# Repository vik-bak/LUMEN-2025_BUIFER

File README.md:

# LUMEN-2025_BUIFER
Development of the hardware and software for smart protection helmet used by construction workers. Three PCBs were design in order to expand the functionalities of the regular protection helmet, code-named after their location on the helmet: BackPCB, FrontPCB and SidePCB. Code written in C, built and loaded into the STM32L476 and ESP Wrover microcontrollers. Implemented local web application developed in React to visualize data from sensors and to notify user about important informations on the construction site. The whole system was tested and proved functional and efficient.

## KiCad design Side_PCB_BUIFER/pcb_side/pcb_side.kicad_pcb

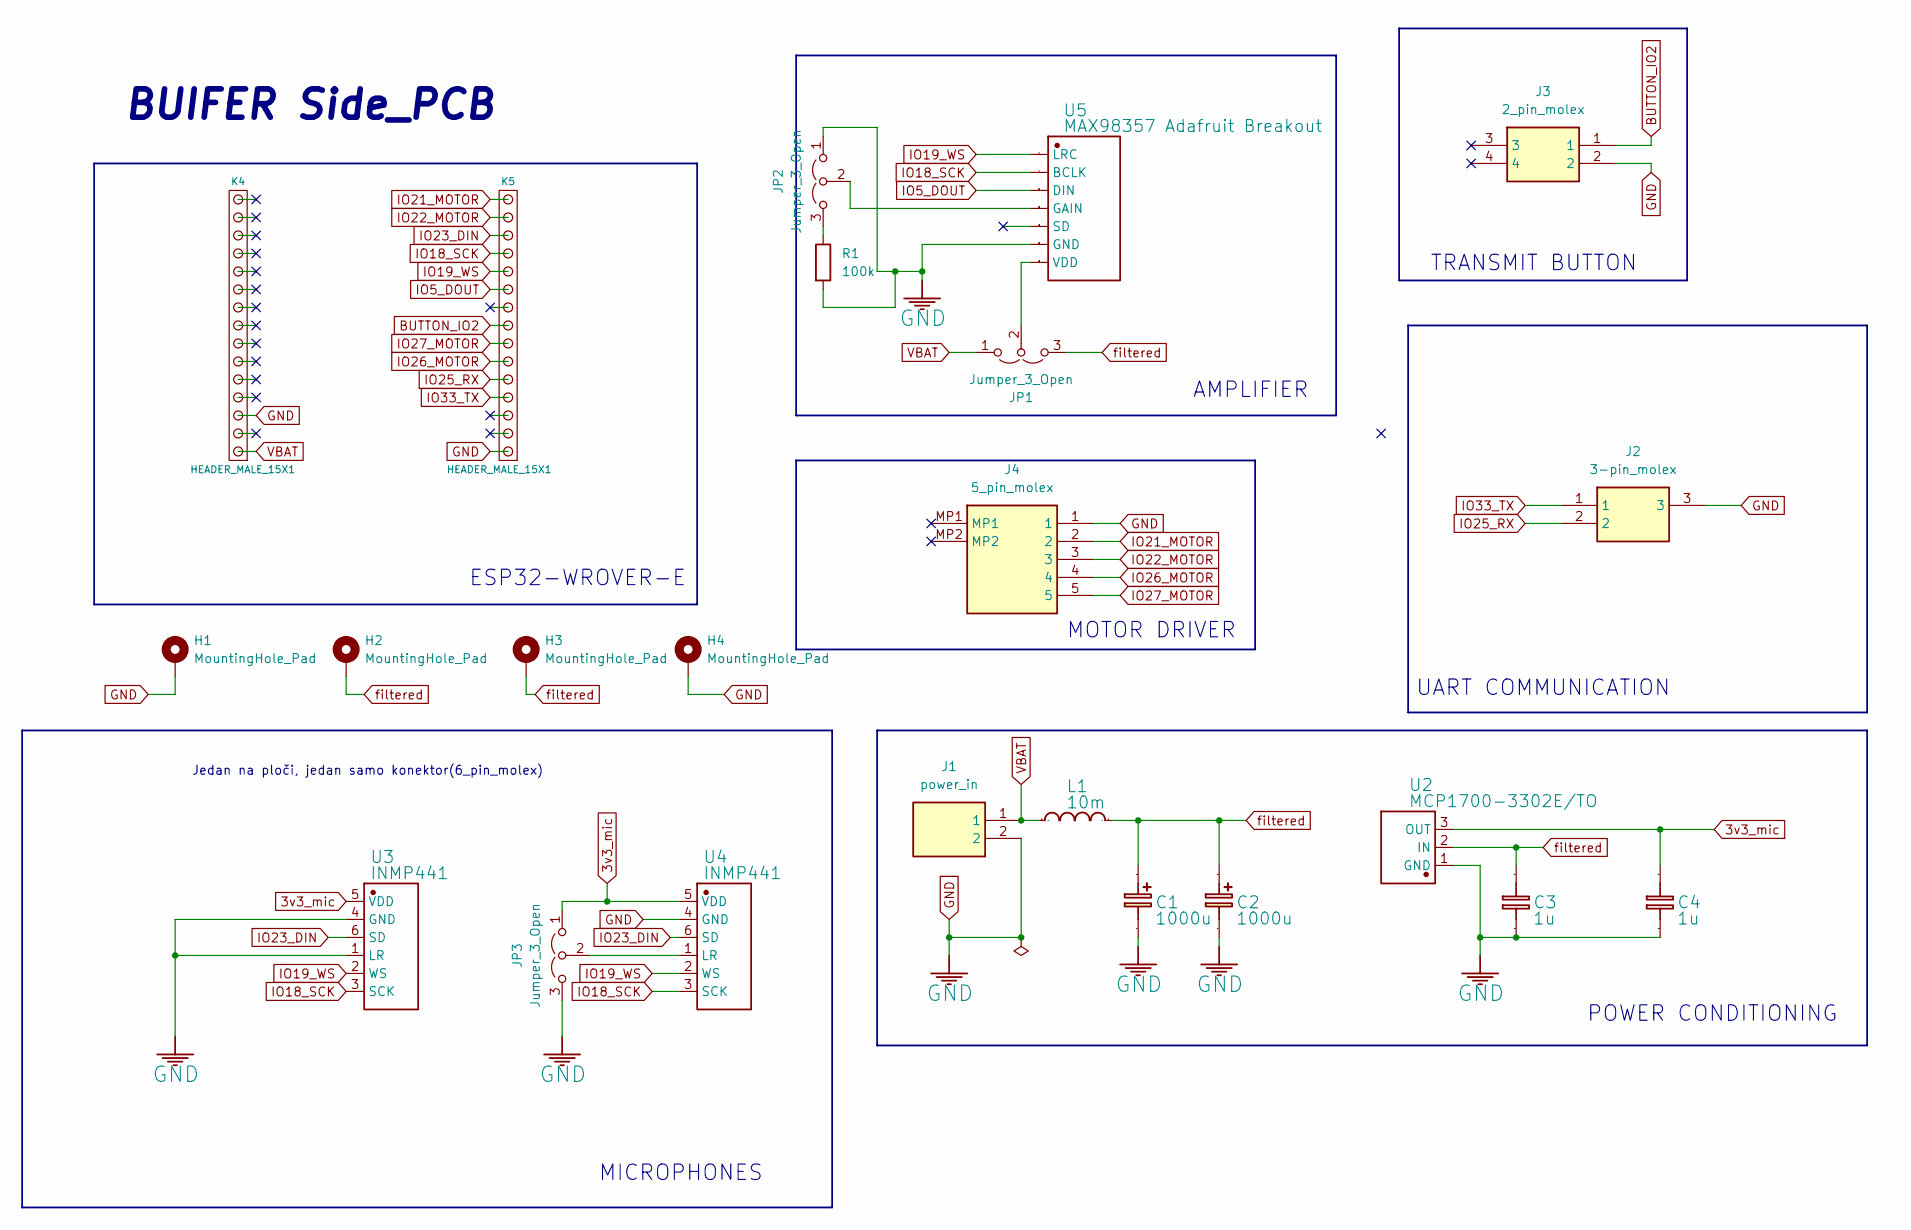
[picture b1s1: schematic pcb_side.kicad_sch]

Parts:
C1, C2: 1000u; CP_Elec_10x12.5
C3, C4: 1u; C_0603_1608Metric_Pad1.08x0.95mm_HandSolder
H1, H2, H3, H4: MountingHole_Pad; MountingHole_2.5mm_Pad_Via
J1: power_in; Mouser Part Number 538-215760-3002
J2: 3-pin_molex; 3_pin_molex; Mouser Part Number 538-53398-0376
J3: 2_pin_molex; Mouser Part Number 538-53398-0276
J4: 5_pin_molex; Mouser Part Number 538-53261-0571
JP1, JP2, JP3: Jumper_3_Open; PinHeader_1x03_P1.27mm_Vertical
K4, K5: HEADER_MALE_15X1; PinSocket_1x15_P2.54mm_Vertical
L1: 10m; L_Radial_D8.7mm_P5.00mm_Fastron_07HCP
R1: 100k; R_0603_1608Metric_Pad0.98x0.95mm_HandSolder
U2: MCP1700-3302E/TO; 3v3_ldo; Manufacturer Part MCP1700-3302E/TO
U3: INMP441; 6_pin_molex
U4: INMP441
U5: MAX98357 Adafruit Breakout; MAX98357A ADAFRUIT

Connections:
3v3_mic: C4.2, JP3.1 (A), U2.3 (OUT), U3.5 (VDD), U4.5 (VDD)
BUTTON_IO2: J3.1, K5.8
GND: C1.2, C2.2, C3.1, C4.1, H1.1, H4.1, J1.2, J2.3, J3.2, J4.1, JP2.1 (A), JP3.3 (B), K4.3, K5.1, R1.2, U2.1 (GND), U3.1 (LR), U3.4 (GND), U4.4 (GND), U5.13 (GND)
IO5_DOUT: K5.10, U5.10 (DIN)
IO18_SCK: K5.12, U3.3 (SCK), U4.3 (SCK), U5.9 (BCLK)
IO19_WS: K5.11, U3.2 (WS), U4.2 (WS), U5.8 (LRC)
IO21_MOTOR: J4.2, K5.15
IO22_MOTOR: J4.3, K5.14
IO23_DIN: K5.13, U3.6 (SD), U4.6 (SD)
IO25_RX: J2.2, K5.5
IO26_MOTOR: J4.4, K5.6
IO27_MOTOR: J4.5, K5.7
IO33_TX: J2.1, K5.4
unnamed: JP1.2 (C), U5.14 (VDD)
unnamed: JP2.3 (B), R1.1
unnamed: JP2.2 (C), U5.11 (GAIN)
unnamed: JP3.2 (C), U4.1 (LR)
VBAT: J1.1, JP1.1 (A), K4.1, L1.1
filtered: C1.1, C2.1, C3.2, H2.1, H3.1, JP1.3 (B), L1.2, U2.2 (IN)

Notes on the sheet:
AMPLIFIER
TRANSMIT BUTTON
Jedan na ploči, jedan samo konektor(6_pin_molex)
ESP32-WROVER-E
BUIFER Side_PCB
MOTOR DRIVER
UART COMMUNICATION
POWER CONDITIONING
MICROPHONES

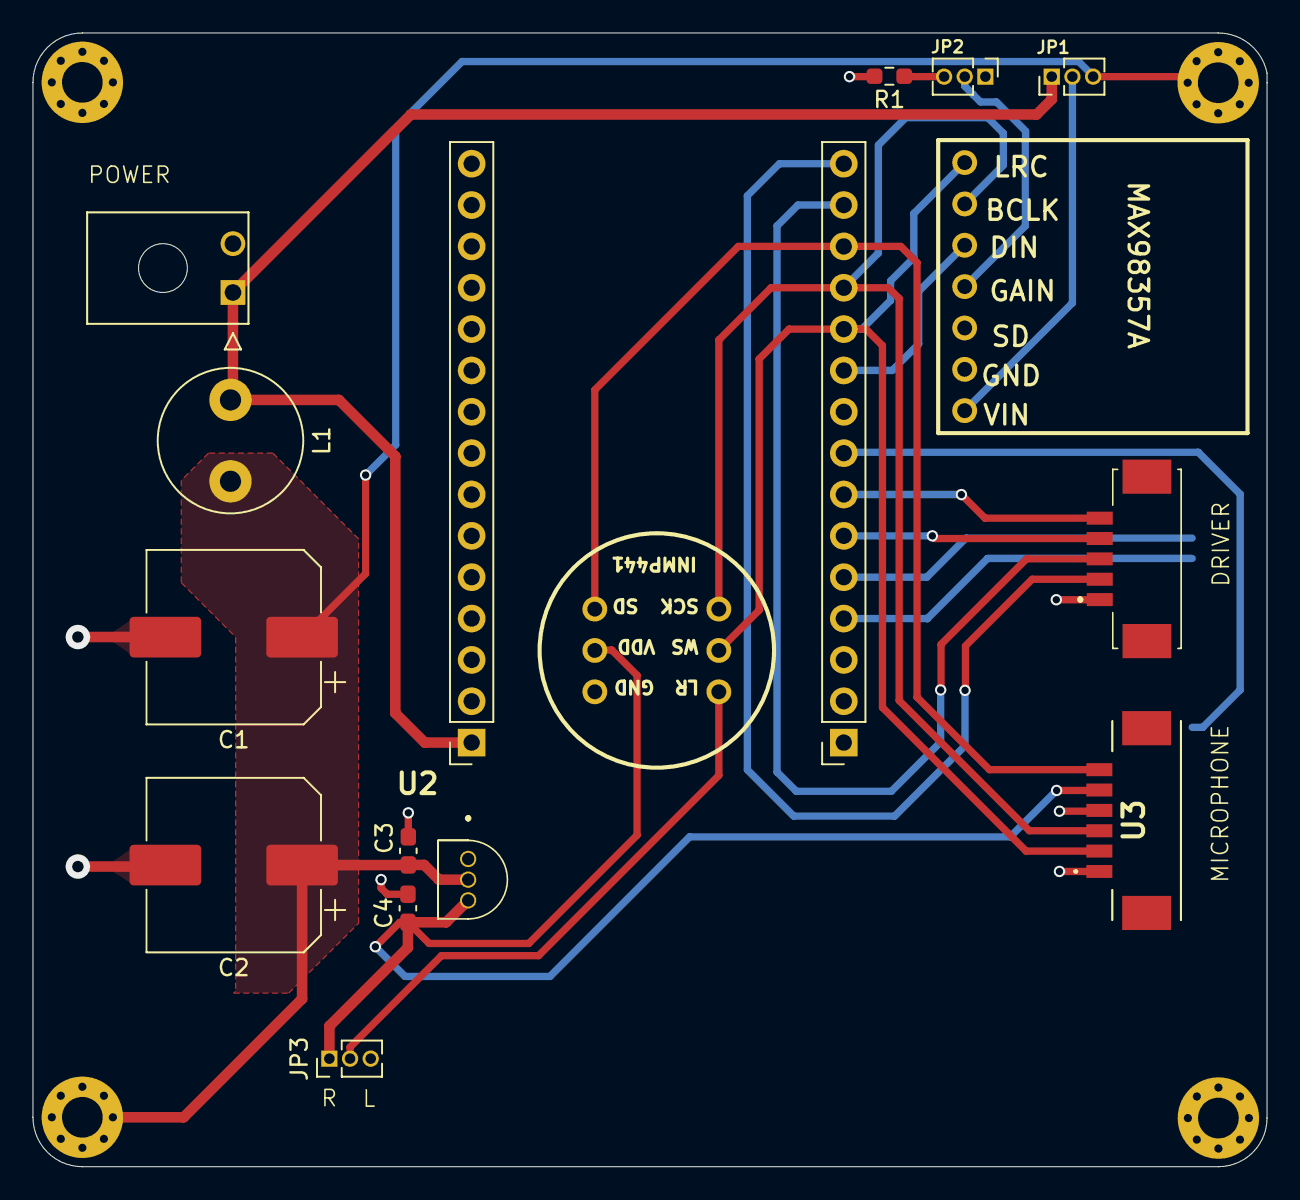
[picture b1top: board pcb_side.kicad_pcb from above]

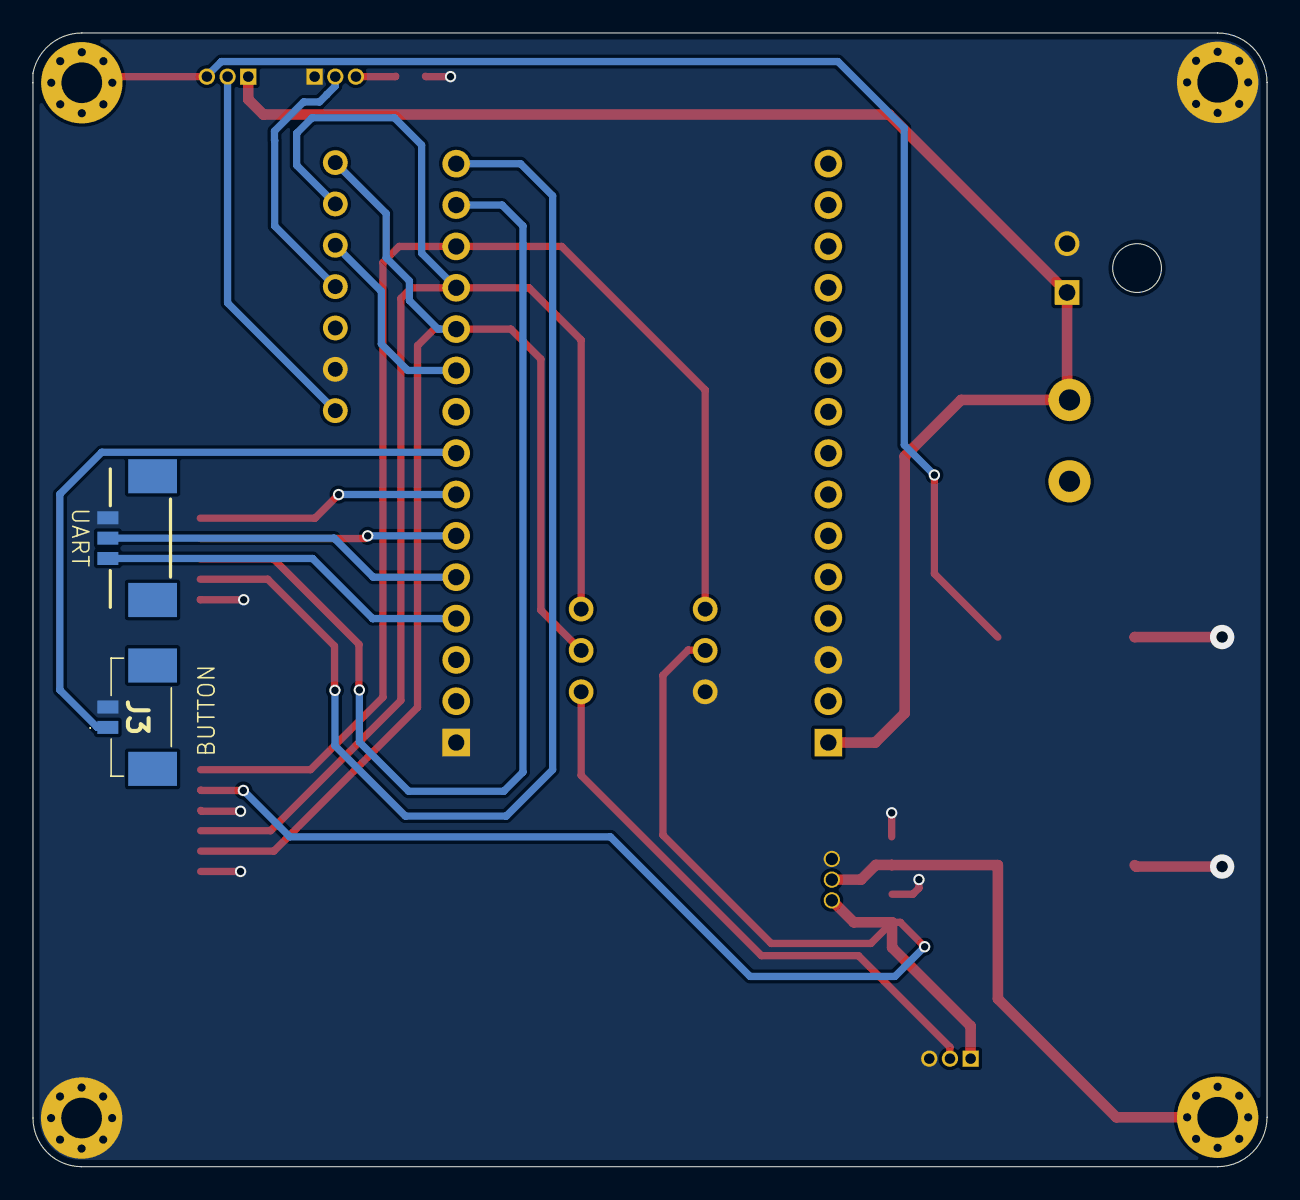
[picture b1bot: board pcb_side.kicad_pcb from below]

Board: 2 copper layers, 75.8 x 69.6 mm, 23 parts (2 on the bottom side), 19 nets.

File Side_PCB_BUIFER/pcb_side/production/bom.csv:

Designator,Footprint,Quantity,Value,LCSC Part #
"C1, C2",CP_Elec_10x12.5,2,1000u,
"C3, C4",0603,2,1u,
"H1, H2, H3, H4",MountingHole_2.5mm_Pad_Via,4,MountingHole_Pad,
J1,power_in,1,power_in,
J2,3_pin_molex,1,3-pin_molex,
J3,2_pin_molex,1,2_pin_molex,
J4,5_pin_molex,1,5_pin_molex,
"JP1, JP2, JP3",PinHeader_1x03_P1.27mm_Vertical,3,Jumper_3_Open,
"K4, K5",PinSocket_1x15_P2.54mm_Vertical,2,HEADER_MALE_15X1,
L1,L_Radial_D8.7mm_P5.00mm_Fastron_07HCP,1,10m,
R1,0603,1,100k,
U2,3v3_ldo,1,MCP1700-3302E/TO,
U3,6_pin_molex,1,INMP441,
U4,INMP441,1,INMP441,
U5,MAX98357A ADAFRUIT,1,MAX98357 Adafruit Breakout,

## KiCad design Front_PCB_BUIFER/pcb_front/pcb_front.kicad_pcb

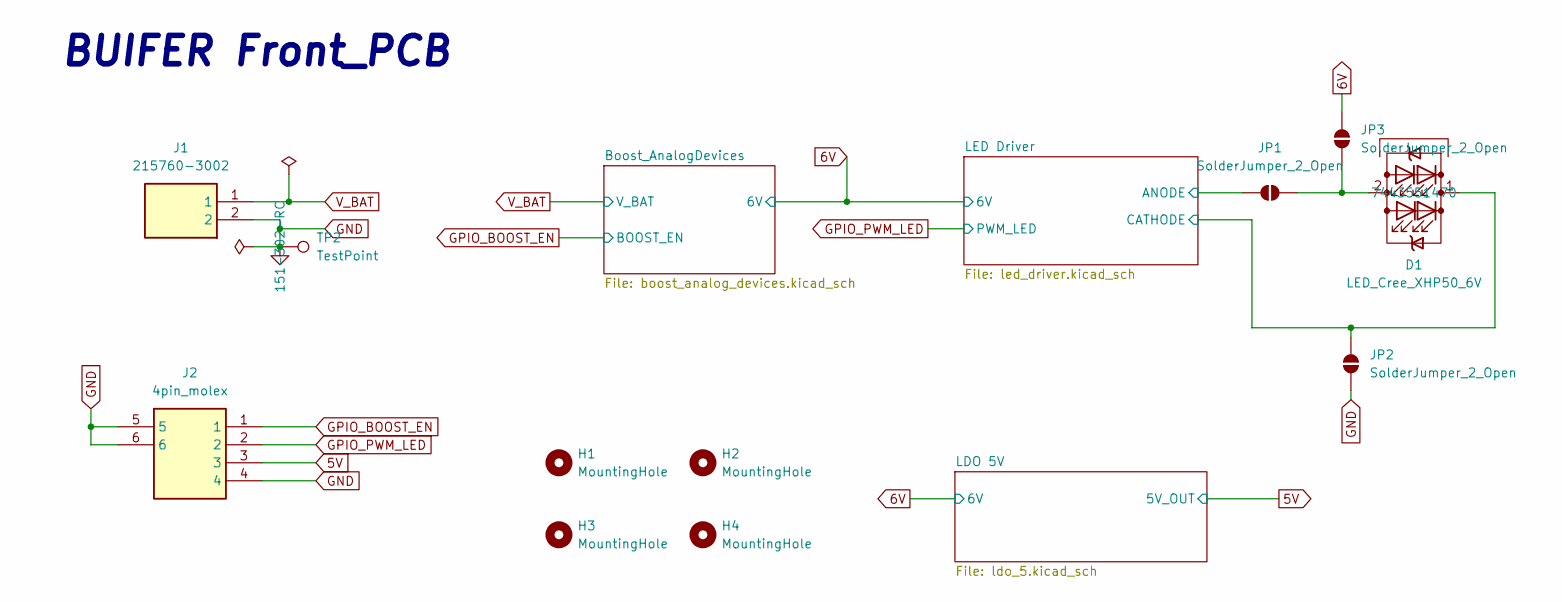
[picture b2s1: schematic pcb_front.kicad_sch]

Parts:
D1: LED_Cree_XHP50_6V; LED_Cree-XHP50_6V; Manufacturer_Part_Number 7443551470
H1, H2, H3, H4: MountingHole; MountingHole_2.2mm_M2_ISO7380
J1: 215760-3002; 215760-YY02; Mouser Part Number 538-215760-3002
J2: 4pin_molex; 4_pin_molex; Mouser Part Number 538-53398-0471
JP1, JP2, JP3: SolderJumper_2_Open; SolderJumper-2_P1.3mm_Open_RoundedPad1.0x1.5mm
TP2: TestPoint; TestPoint_Loop_D2.54mm_Drill1.5mm_Beaded; Manufacturer_Part_Number 151-302-RC

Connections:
5V: J2.3; also elsewhere on the board
6V: JP3.2 (B); also elsewhere on the board
/LED Driver/ANODE: JP1.1 (A); also elsewhere on the board
/LED Driver/CATHODE: D1.1 (K), JP2.2 (B); also elsewhere on the board
GND: J1.2, J2.4, J2.5, J2.6, JP2.1 (A), TP2.1; also elsewhere on the board
GPIO_BOOST_EN: J2.1; also elsewhere on the board
GPIO_PWM_LED: J2.2; also elsewhere on the board
unnamed: D1.2 (A), JP1.2 (B), JP3.1 (A)
V_BAT: J1.1; also elsewhere on the board

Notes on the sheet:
BUIFER Front_PCB

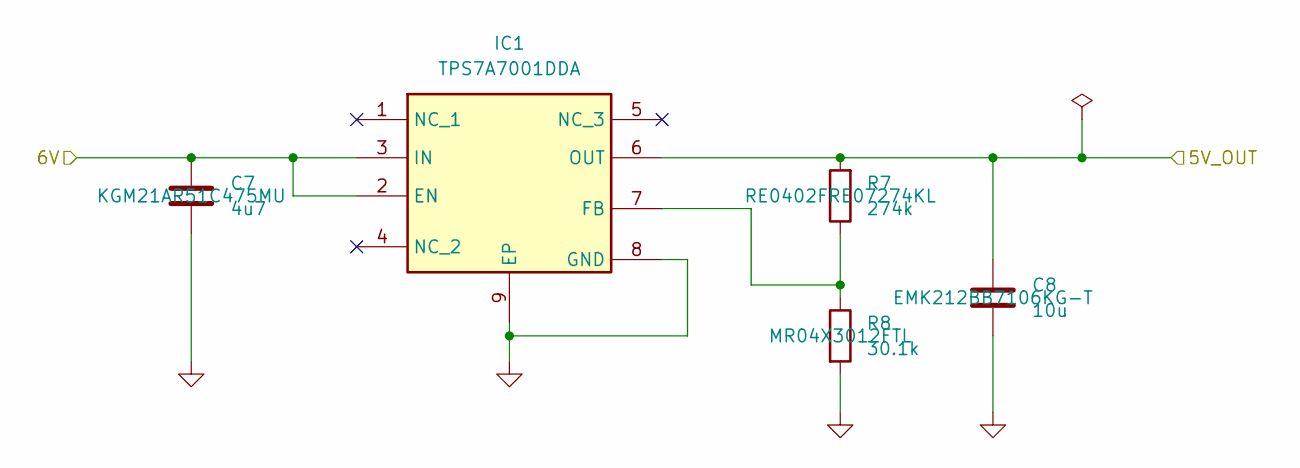
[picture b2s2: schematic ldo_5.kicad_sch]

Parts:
C7: 4u7; C_0805_2012Metric_Pad1.18x1.45mm_HandSolder; Manufacturer_Part_Number KGM21AR51C475MU
C8: 10u; C_0805_2012Metric_Pad1.18x1.45mm_HandSolder; Manufacturer_Part_Number EMK212BB7106KG-T
IC1: TPS7A7001DDA; LDO_5V; Mouser Part Number 595-TPS7A7001DDA
R7: 274k; R_0402_1005Metric_Pad0.72x0.64mm_HandSolder; Manufacturer_Part_Number RE0402FRE07274KL
R8: 30.1k; R_0402_1005Metric_Pad0.72x0.64mm_HandSolder; Manufacturer_Part_Number MR04X3012FTL

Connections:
5V: C8.1, IC1.6 (OUT), R7.2; also elsewhere on the board
6V: C7.1, IC1.2 (EN), IC1.3 (IN); also elsewhere on the board
GND: C7.2, C8.2, IC1.8 (GND), IC1.9 (EP), R8.2; also elsewhere on the board
unnamed: IC1.7 (FB), R7.1, R8.1

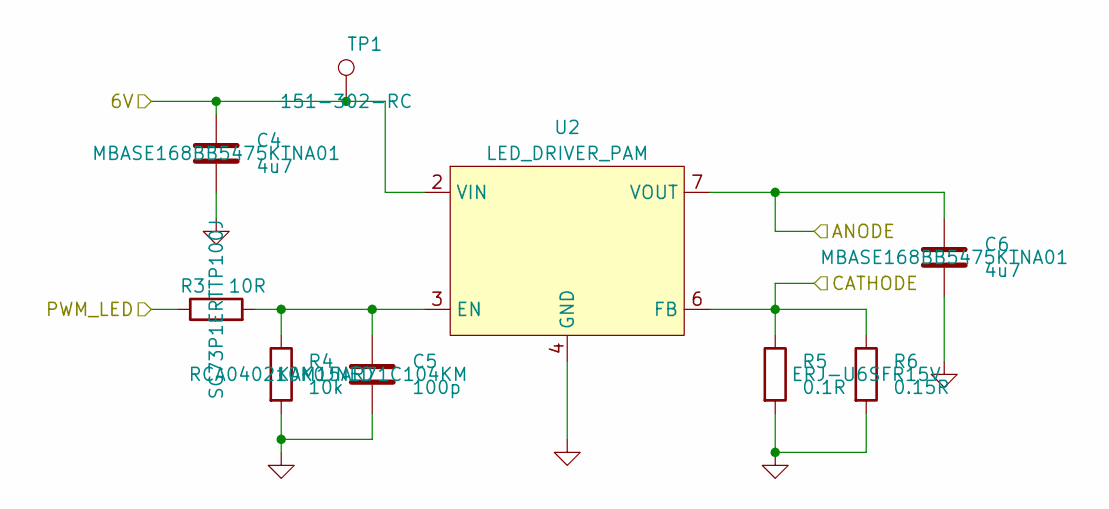
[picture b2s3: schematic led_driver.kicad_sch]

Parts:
C4, C6: 4u7; C_0603_1608Metric_Pad1.08x0.95mm_HandSolder; Manufacturer_Part_Number MBASE168BB5475KTNA01
C5: 100p; C_0603_1608Metric_Pad1.08x0.95mm_HandSolder; Manufacturer_Part_Number KAM15AR71C104KM
R3: 10R; R_0402_1005Metric_Pad0.72x0.64mm_HandSolder; Manufacturer_Part_Number SG73P1ERTTP100J
R4: 10k; R_0402_1005Metric_Pad0.72x0.64mm_HandSolder; Manufacturer_Part_Number RCA040210K0JNED
R5: 0.1R; R_0805_2012Metric_Pad1.20x1.40mm_HandSolder; Manufacturer_Part_Number ERJ-U6SFR10V
R6: 0.15R; R_0805_2012Metric_Pad1.20x1.40mm_HandSolder; Manufacturer_Part_Number ERJ-U6SFR15V
TP1: TestPoint; TestPoint_Loop_D2.54mm_Drill1.5mm_Beaded; Manufacturer_Part_Number 151-302-RC
U2: LED_DRIVER_PAM; Diodes_SO-8EP

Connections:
6V: C4.1, TP1.1, U2.2 (VIN); also elsewhere on the board
/LED Driver/ANODE: C6.1, U2.7 (VOUT); also elsewhere on the board
/LED Driver/CATHODE: R5.1, R6.1, U2.6 (FB); also elsewhere on the board
GND: C4.2, C5.2, C6.2, R4.2, R5.2, R6.2, U2.4 (GND); also elsewhere on the board
GPIO_PWM_LED: R3.1; also elsewhere on the board
unnamed: C5.1, R3.2, R4.1, U2.3 (EN)

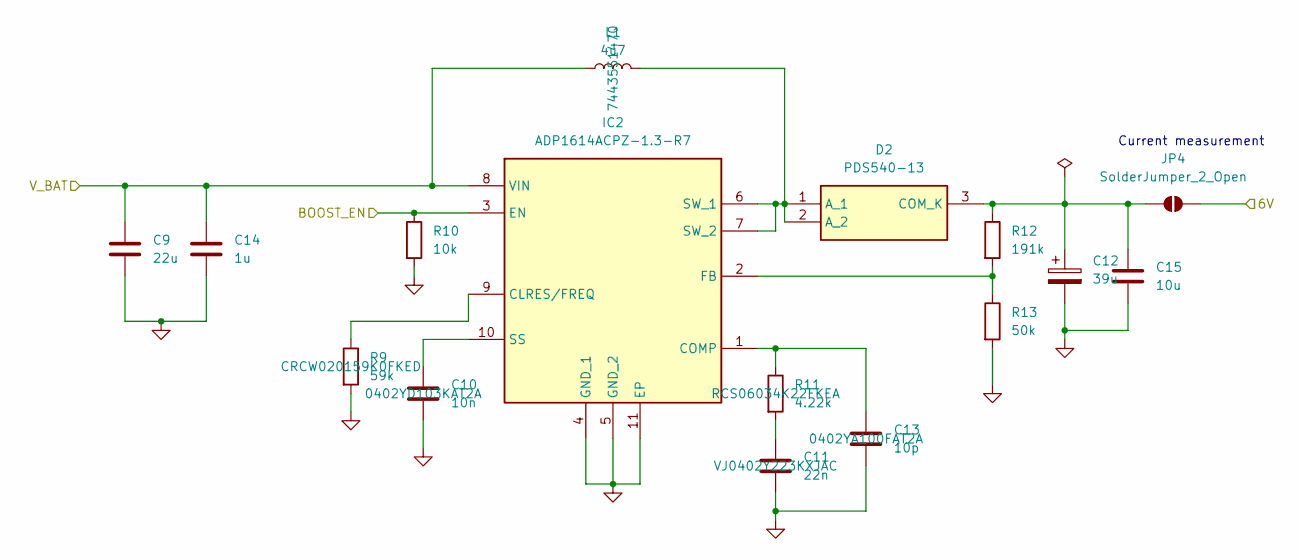
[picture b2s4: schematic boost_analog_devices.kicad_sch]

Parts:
C9: 22u; C_1206_3216Metric_Pad1.33x1.80mm_HandSolder; Manufacturer_Part_Number EMK316BJ226ML-T
C10: 10n; C_0402_1005Metric_Pad0.74x0.62mm_HandSolder; Manufacturer_Part_Number 0402YD103KAT2A
C11: 22n; C_0402_1005Metric_Pad0.74x0.62mm_HandSolder; Manufacturer_Part_Number VJ0402Y223KXJAC
C12: 39u; CAP_RPS&slash_PA_6P3X5P7_NCH; Manufacturer_Part_Number RPA1C390MCN1GS
C13: 10p; C_0402_1005Metric_Pad0.74x0.62mm_HandSolder; Manufacturer_Part_Number 0402YA100FAT2A
C14: 1u; C_0603_1608Metric_Pad1.08x0.95mm_HandSolder; Manufacturer_Part_Number GRM188R61A105KA61D
C15: 10u; C_0603_1608Metric_Pad1.08x0.95mm_HandSolder; Manufacturer_Part_Number KGM15CR51C106KT
D2: PDS540-13; Schottky_Diode; Mouser Part Number 621-PDS540-13
IC2: ADP1614ACPZ-1.3-R7; Boost_Converter_AD; Mouser Part Number 584-ADP1614ACPZ1.3R7
JP4: SolderJumper_2_Open; SolderJumper-2_P1.3mm_Open_RoundedPad1.0x1.5mm
L1: 4u7; WE-HCI_1350_136523; Manufacturer_Part_Number 7443551470
R9: 59k; R_0603_1608Metric_Pad0.98x0.95mm_HandSolder; Manufacturer_Part_Number CRCW020159K0FKED
R10: 10k; R_0402_1005Metric_Pad0.72x0.64mm_HandSolder; Manufacturer_Part_Number RCA040210K0JNED
R11: 4.22k; R_0603_1608Metric_Pad0.98x0.95mm_HandSolder; Manufacturer_Part_Number RCS06034K22FKEA
R12: 191k; R_0603_1608Metric_Pad0.98x0.95mm_HandSolder; Manufacturer_Part_Number RR0816P-1913-D-28D
R13: 50k; R_0603_1608Metric_Pad0.98x0.95mm_HandSolder; Manufacturer_Part_Number RT0603BRD0750KL

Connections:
6V: JP4.2 (B); also elsewhere on the board
GND: C9.2, C10.2, C11.2, C12.2, C13.2, C14.2, C15.2, IC2.4 (GND_1), IC2.5 (GND_2), IC2.11 (EP), R9.2, R10.2, R13.2; also elsewhere on the board
GPIO_BOOST_EN: IC2.3 (EN), R10.1; also elsewhere on the board
unnamed: C11.1, R11.2
unnamed: D2.1 (A_1), D2.2 (A_2), IC2.6 (SW_1), IC2.7 (SW_2), L1.2
unnamed: C12.1, C15.1, D2.3 (COM_K), JP4.1 (A), R12.1
unnamed: IC2.9 (CLRES/FREQ), R9.1
unnamed: C13.1, IC2.1 (COMP), R11.1
unnamed: IC2.2 (FB), R12.2, R13.1
unnamed: C10.1, IC2.10 (SS)
V_BAT: C9.1, C14.1, IC2.8 (VIN), L1.1; also elsewhere on the board

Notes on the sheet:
Current measurement

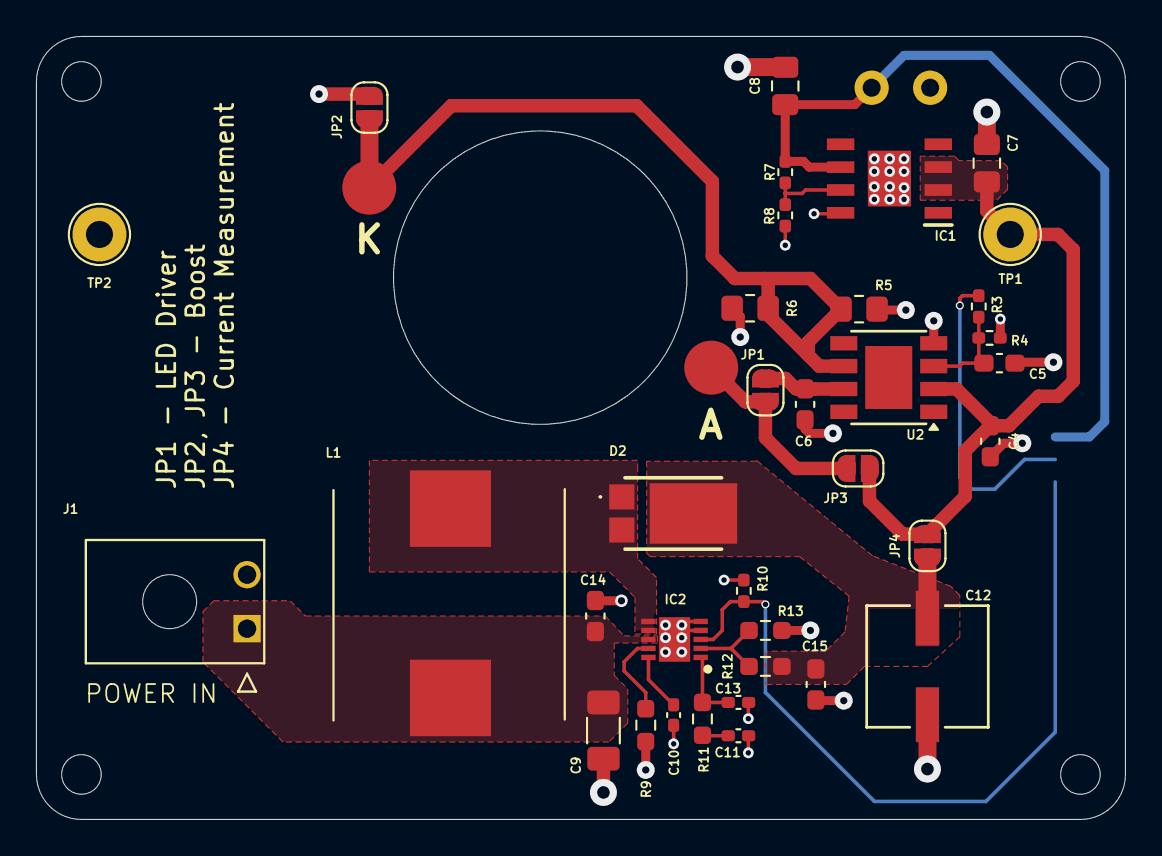
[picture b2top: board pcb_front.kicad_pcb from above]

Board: 2 copper layers, 60.5 x 43.5 mm, 41 parts (1 on the bottom side), 18 nets.

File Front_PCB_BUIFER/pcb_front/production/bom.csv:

Designator,Footprint,Quantity,Value,LCSC Part #
,,1,,
C10,0402,1,10n,
C11,0402,1,22n,
C12,CAP_RPS&slash_PA_6P3X5P7_NCH,1,39u,
C13,0402,1,10p,
C14,0603,1,1u,
C15,0603,1,10u,
"C4, C6",0603,2,4u7,
C5,0603,1,100p,
C7,0805,1,4u7,
C8,0805,1,10u,
C9,1206,1,22u,
D1,LED_Cree-XHP50_6V,1,LED_Cree_XHP50_6V,
D2,Schottky_Diode,1,PDS540-13,
IC1,LDO_5V,1,TPS7A7001DDA,
IC2,Boost_Converter_AD,1,ADP1614ACPZ-1.3-R7,
J1,215760-YY02,1,215760-3002,
J2,4_pin_molex,1,4pin_molex,
L1,WE-HCI_1350_136523,1,4u7,
"R10, R4",0402,2,10k,
R11,0603,1,4.22k,
R12,0603,1,191k,
R13,0603,1,50k,
R3,0402,1,10R,
R5,0805,1,0.1R,
R6,0805,1,0.15R,
R7,0402,1,274k,
R8,0402,1,30.1k,
R9,0603,1,59k,
"TP1, TP2",TestPoint_Loop_D2.54mm_Drill1.5mm_Beaded,2,TestPoint,
U2,Diodes_SO-8EP,1,LED_DRIVER_PAM,

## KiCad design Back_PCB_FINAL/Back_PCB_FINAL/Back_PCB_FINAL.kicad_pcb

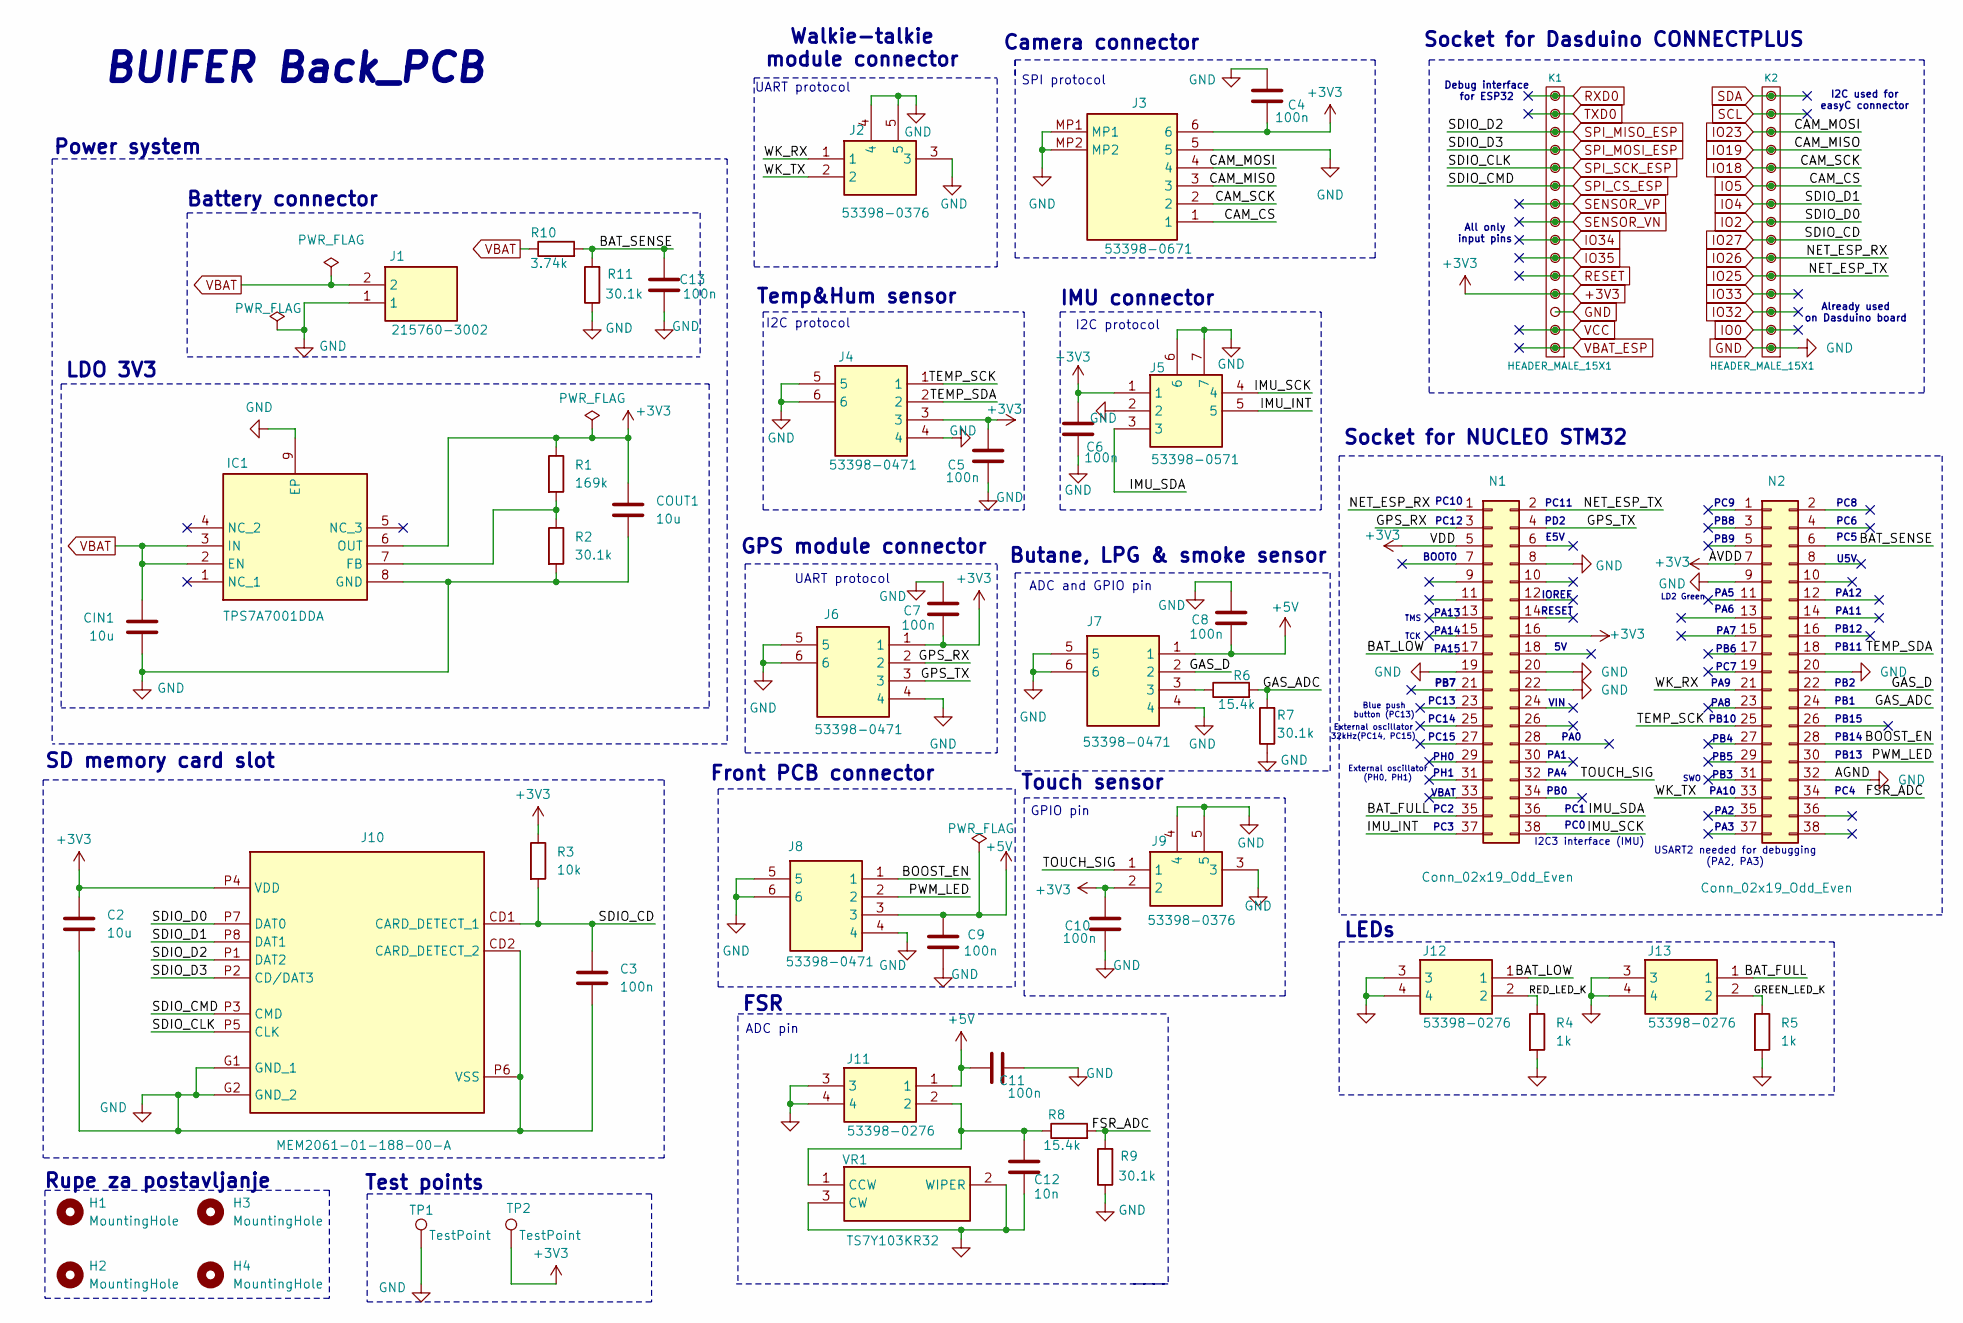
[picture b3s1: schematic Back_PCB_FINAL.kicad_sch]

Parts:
C2: 10u; C_0603_1608Metric_Pad1.08x0.95mm_HandSolder
C3, C4, C5, C6, C7, C8, C9, C10, C11, C13: 100n; C_0603_1608Metric_Pad1.08x0.95mm_HandSolder
C12: 10n; C_0603_1608Metric_Pad1.08x0.95mm_HandSolder
CIN1: 10u; C_0603_1608Metric_Pad1.08x0.95mm_HandSolder
COUT1: 10u; C_0603_1608Metric_Pad1.08x0.95mm_HandSolder
H1, H2, H3, H4: MountingHole; MountingHole_3.2mm_M3
IC1: TPS7A7001DDA; SOIC127P600X170-9N; Mouser Part Number 595-TPS7A7001DDA
J1: 215760-3002; 215760-YY02; Mouser Part Number 538-215760-3002
J2, J9: 53398-0376; 53398-0371; Mouser Part Number 538-53398-0376
J3: 53398-0671; 533980671; Mouser Part Number 538-53398-0671
J4, J6, J7, J8: 53398-0471; 533980471; Mouser Part Number 538-53398-0471
J5: 53398-0571; Mouser Part Number 538-53398-0571
J10: MEM2061-01-188-00-A; MEM20610118800A; Mouser Part Number 640-MEM20610118800A
J11, J12, J13: 53398-0276; 533980276; Mouser Part Number 538-53398-0276
K1, K2: HEADER_MALE_15X1; PinSocket_1x15_P2.54mm_Vertical
N1, N2: Conn_02x19_Odd_Even; Connector_PinSocket_2.54mm_NUCLEO
R1: 169k; R_0603_1608Metric_Pad0.98x0.95mm_HandSolder
R2, R7, R9, R11: 30.1k; R_0603_1608Metric_Pad0.98x0.95mm_HandSolder
R3: 10k; R_0603_1608Metric_Pad0.98x0.95mm_HandSolder
R4, R5: 1k; R_0603_1608Metric_Pad0.98x0.95mm_HandSolder
R6, R8: 15.4k; R_0603_1608Metric_Pad0.98x0.95mm_HandSolder
R10: 3.74k; R_0603_1608Metric_Pad0.98x0.95mm_HandSolder
TP1, TP2: TestPoint; PinHeader_1x01_P2.54mm_Vertical
VR1: TS7Y103KR32; Mouser Part Number 72-TS7Y103KR32

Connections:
+3V3: C2.1, C4.1, C5.1, C6.1, C7.1, C10.1, COUT1.2, IC1.6 (OUT), J3.6, J4.3, J5.1, J6.1, J9.2, J10.P4 (VDD), K1.4, N1.5, N1.16, N2.7, R1.1, R3.1, TP2.1
+5V: C8.1, C9.1, C11.1, J7.1, J8.3, J11.1
/BAT_FULL: J13.1, N1.35
/BAT_LOW: J12.1, N1.17
/BAT_SENSE: C13.1, N2.6, R10.2, R11.2
/BOOST_EN: J8.1, N2.28
/FSR_ADC: N2.34, R8.2, R9.2
/GAS_ADC: N2.24, R6.2, R7.2
/GAS_D: J7.2, N2.22
/GPS_RX: J6.2, N1.3
/GPS_TX: J6.3, N1.4
/GREEN_LED_K: J13.2, R5.1
/IMU_INT: J5.5, N1.37
/IMU_SCK: J5.4, N1.38
/IMU_SDA: J5.3, N1.36
/PWM_LED: J8.2, N2.30
/RED_LED_K: J12.2, R4.1
/TEMP_SCK: J4.1, N2.25
/TEMP_SDA: J4.2, N2.18
/TOUCH_SIG: J9.1, N1.32
/WK_RX: J2.1, N2.21
/WK_TX: J2.2, N2.33
GND: C2.2, C3.2, C4.2, C5.2, C6.2, C7.2, C8.2, C9.2, C10.2, C11.2, C12.2, C13.2, CIN1.2, COUT1.1, IC1.8 (GND), IC1.9 (EP), J1.1, J2.3, J2.4, J2.5, J3.5, J3.MP1, J3.MP2, J4.4, J4.5, J4.6, J5.2, J5.6, J5.7, J6.4, J6.5, J6.6, J7.4, J7.5, J7.6, J8.4, J8.5, J8.6, J9.3, J9.4, J9.5, J10.CD2 (CARD_DETECT_2), J10.G1 (GND_1), J10.G2 (GND_2), J10.P6 (VSS), J11.3, J11.4, J12.3, J12.4, J13.3, J13.4, K1.3, K2.1, N1.8, N1.19, N1.20, N1.22, N2.9, N2.20, N2.32, R2.2, R4.2, R5.2, R7.1, R9.1, R11.1, TP1.1, VR1.2 (WIPER), VR1.3 (CW)
IO0: K2.2
IO2: J10.P7 (DAT0), K2.8
IO4: J10.P8 (DAT1), K2.9
IO5: J3.1, K2.10
IO18: J3.2, K2.11
IO19: J3.3, K2.12
IO23: J3.4, K2.13
IO25: K2.5, N1.2
IO26: K2.6, N1.1
IO27: C3.1, J10.CD1 (CARD_DETECT_1), K2.7, R3.2
IO32: K2.3
IO33: K2.4
IO34: K1.7
IO35: K1.6
unnamed: IC1.7 (FB), R1.2, R2.1
unnamed: J7.3, R6.1
unnamed: C12.1, J11.2, R8.1, VR1.1 (CCW)
RESET: K1.5
RXD0: K1.15
SCL: K2.14
SDA: K2.15
SENSOR_VN: K1.8
SENSOR_VP: K1.9
SPI_CS_ESP: J10.P3 (CMD), K1.10
SPI_MISO_ESP: J10.P1 (DAT2), K1.13
SPI_MOSI_ESP: J10.P2 (CD/DAT3), K1.12
SPI_SCK_ESP: J10.P5 (CLK), K1.11
TXD0: K1.14
VBAT: CIN1.1, IC1.2 (EN), IC1.3 (IN), J1.2, R10.1
VBAT_ESP: K1.1
VCC: K1.2

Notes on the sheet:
PC0
USART2 needed for debugging (PA2, PA3)
I2C3 interface (IMU)
PB1
BOOT0
ADC pin
PA6
IOREF
PB14
PA8
PB0
Butane, LPG & smoke sensor
PB12
PC11
PB8
Socket for Dasduino CONNECTPLUS
PH0
PB7
PC2
PD2
TCK
PA7
PC10
UART protocol
PB4
PC15
SD memory card slot
PB2
PA11
External oscillator (PH0, PH1)
SPI protocol
FSR
PC8
PA1
Blue push button (PC13)
Camera connector
PC13
PB15
I2C protocol
E5V

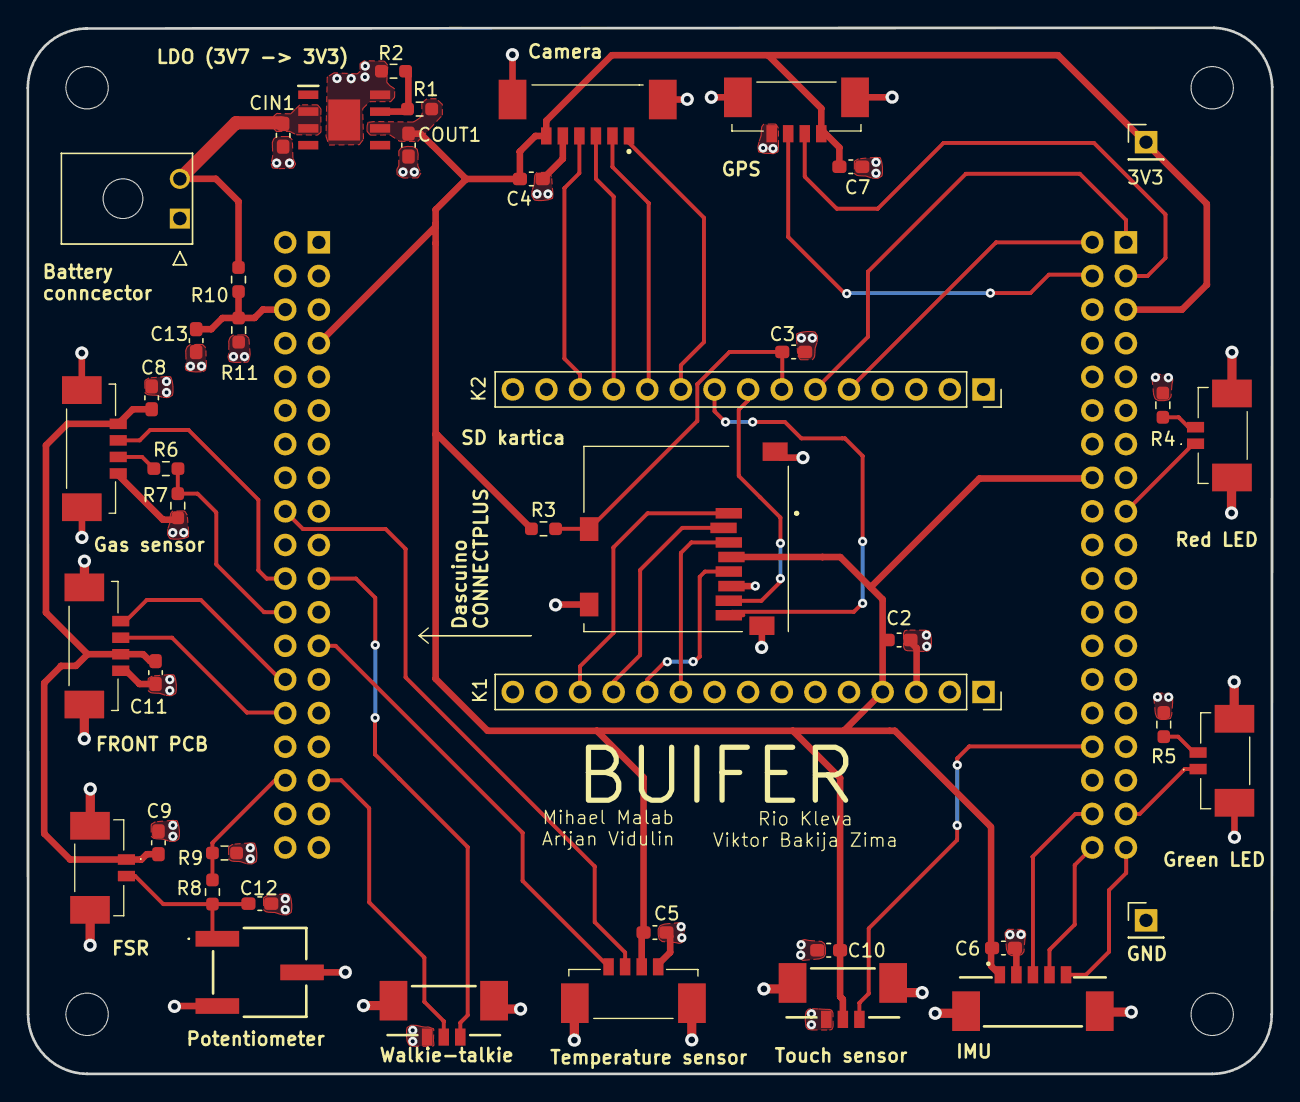
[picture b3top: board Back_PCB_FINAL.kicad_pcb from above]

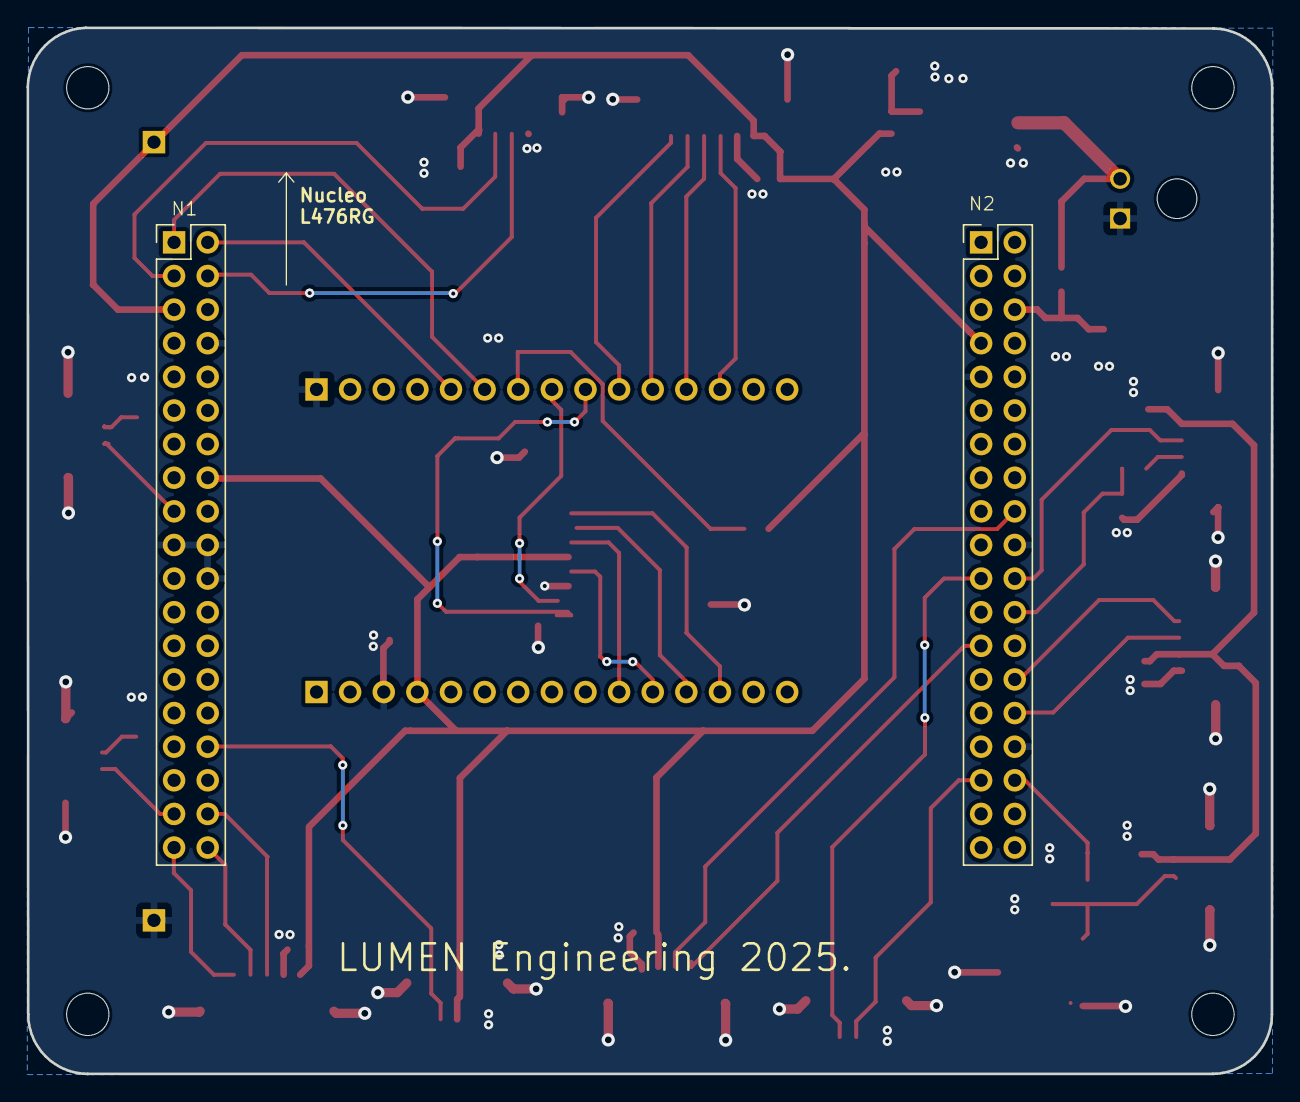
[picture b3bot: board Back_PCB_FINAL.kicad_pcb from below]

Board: 2 copper layers, 94.0 x 79.0 mm, 50 parts (2 on the bottom side), 40 nets.

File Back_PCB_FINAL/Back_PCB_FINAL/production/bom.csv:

Designator,Footprint,Quantity,Value,LCSC Part #
"C10, C11, C13, C3, C4, C5, C6, C7, C8, C9",0603,10,100n,
C12,0603,1,10n,
"C2, CIN1, COUT1",0603,3,10u,
"H1, H2, H3, H4",MountingHole_3.2mm_M3,4,MountingHole,
IC1,SOIC127P600X170-9N,1,TPS7A7001DDA,
J1,215760-YY02,1,215760-3002,
J10,MEM20610118800A,1,MEM2061-01-188-00-A,
"J11, J12, J13",533980276,3,53398-0276,
"J2, J9",53398-0371,2,53398-0376,
J3,533980671,1,53398-0671,
"J4, J6, J7, J8",533980471,4,53398-0471,
J5,53398-0571,1,53398-0571,
"K1, K2",PinSocket_1x15_P2.54mm_Vertical,2,HEADER_MALE_15X1,
"N1, N2",Connector_PinSocket_2.54mm_NUCLEO,2,Conn_02x19_Odd_Even,
R1,0603,1,169k,
R10,0603,1,3.74k,
"R11, R2, R7, R9",0603,4,30.1k,
R3,0603,1,10k,
"R4, R5",0603,2,1k,
"R6, R8",0603,2,15.4k,
"TP1, TP2",PinHeader_1x01_P2.54mm_Vertical,2,TestPoint,
VR1,TS7Y103KR32,1,TS7Y103KR32,
